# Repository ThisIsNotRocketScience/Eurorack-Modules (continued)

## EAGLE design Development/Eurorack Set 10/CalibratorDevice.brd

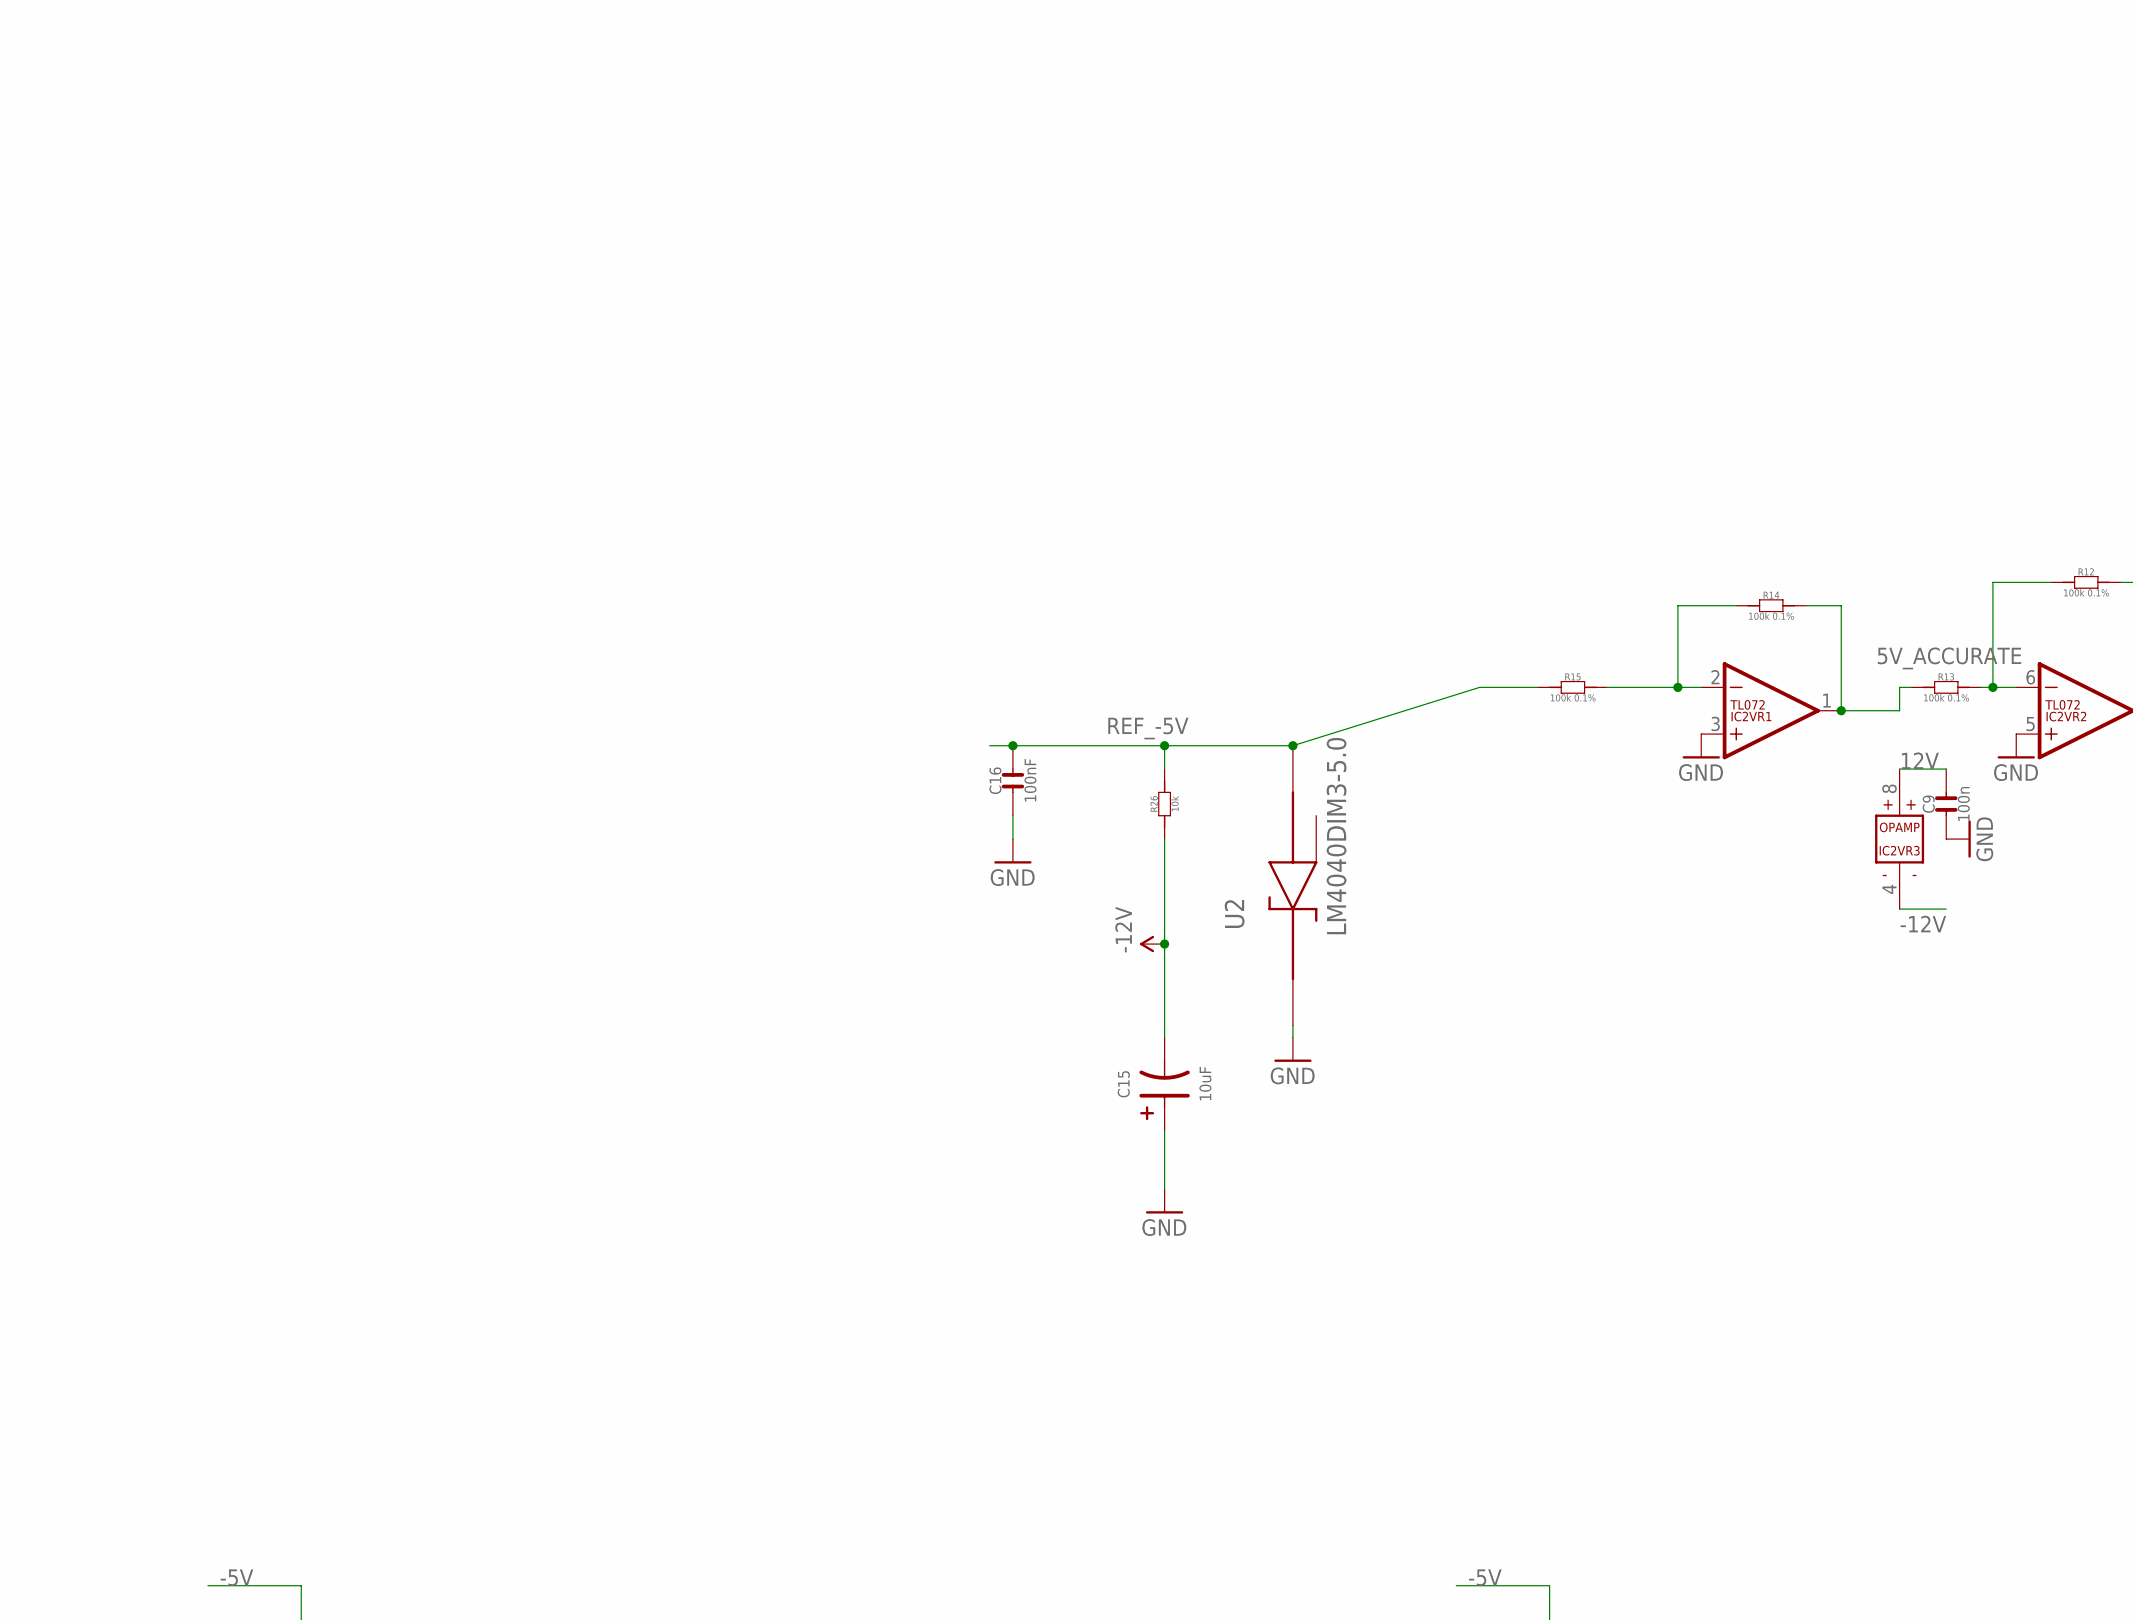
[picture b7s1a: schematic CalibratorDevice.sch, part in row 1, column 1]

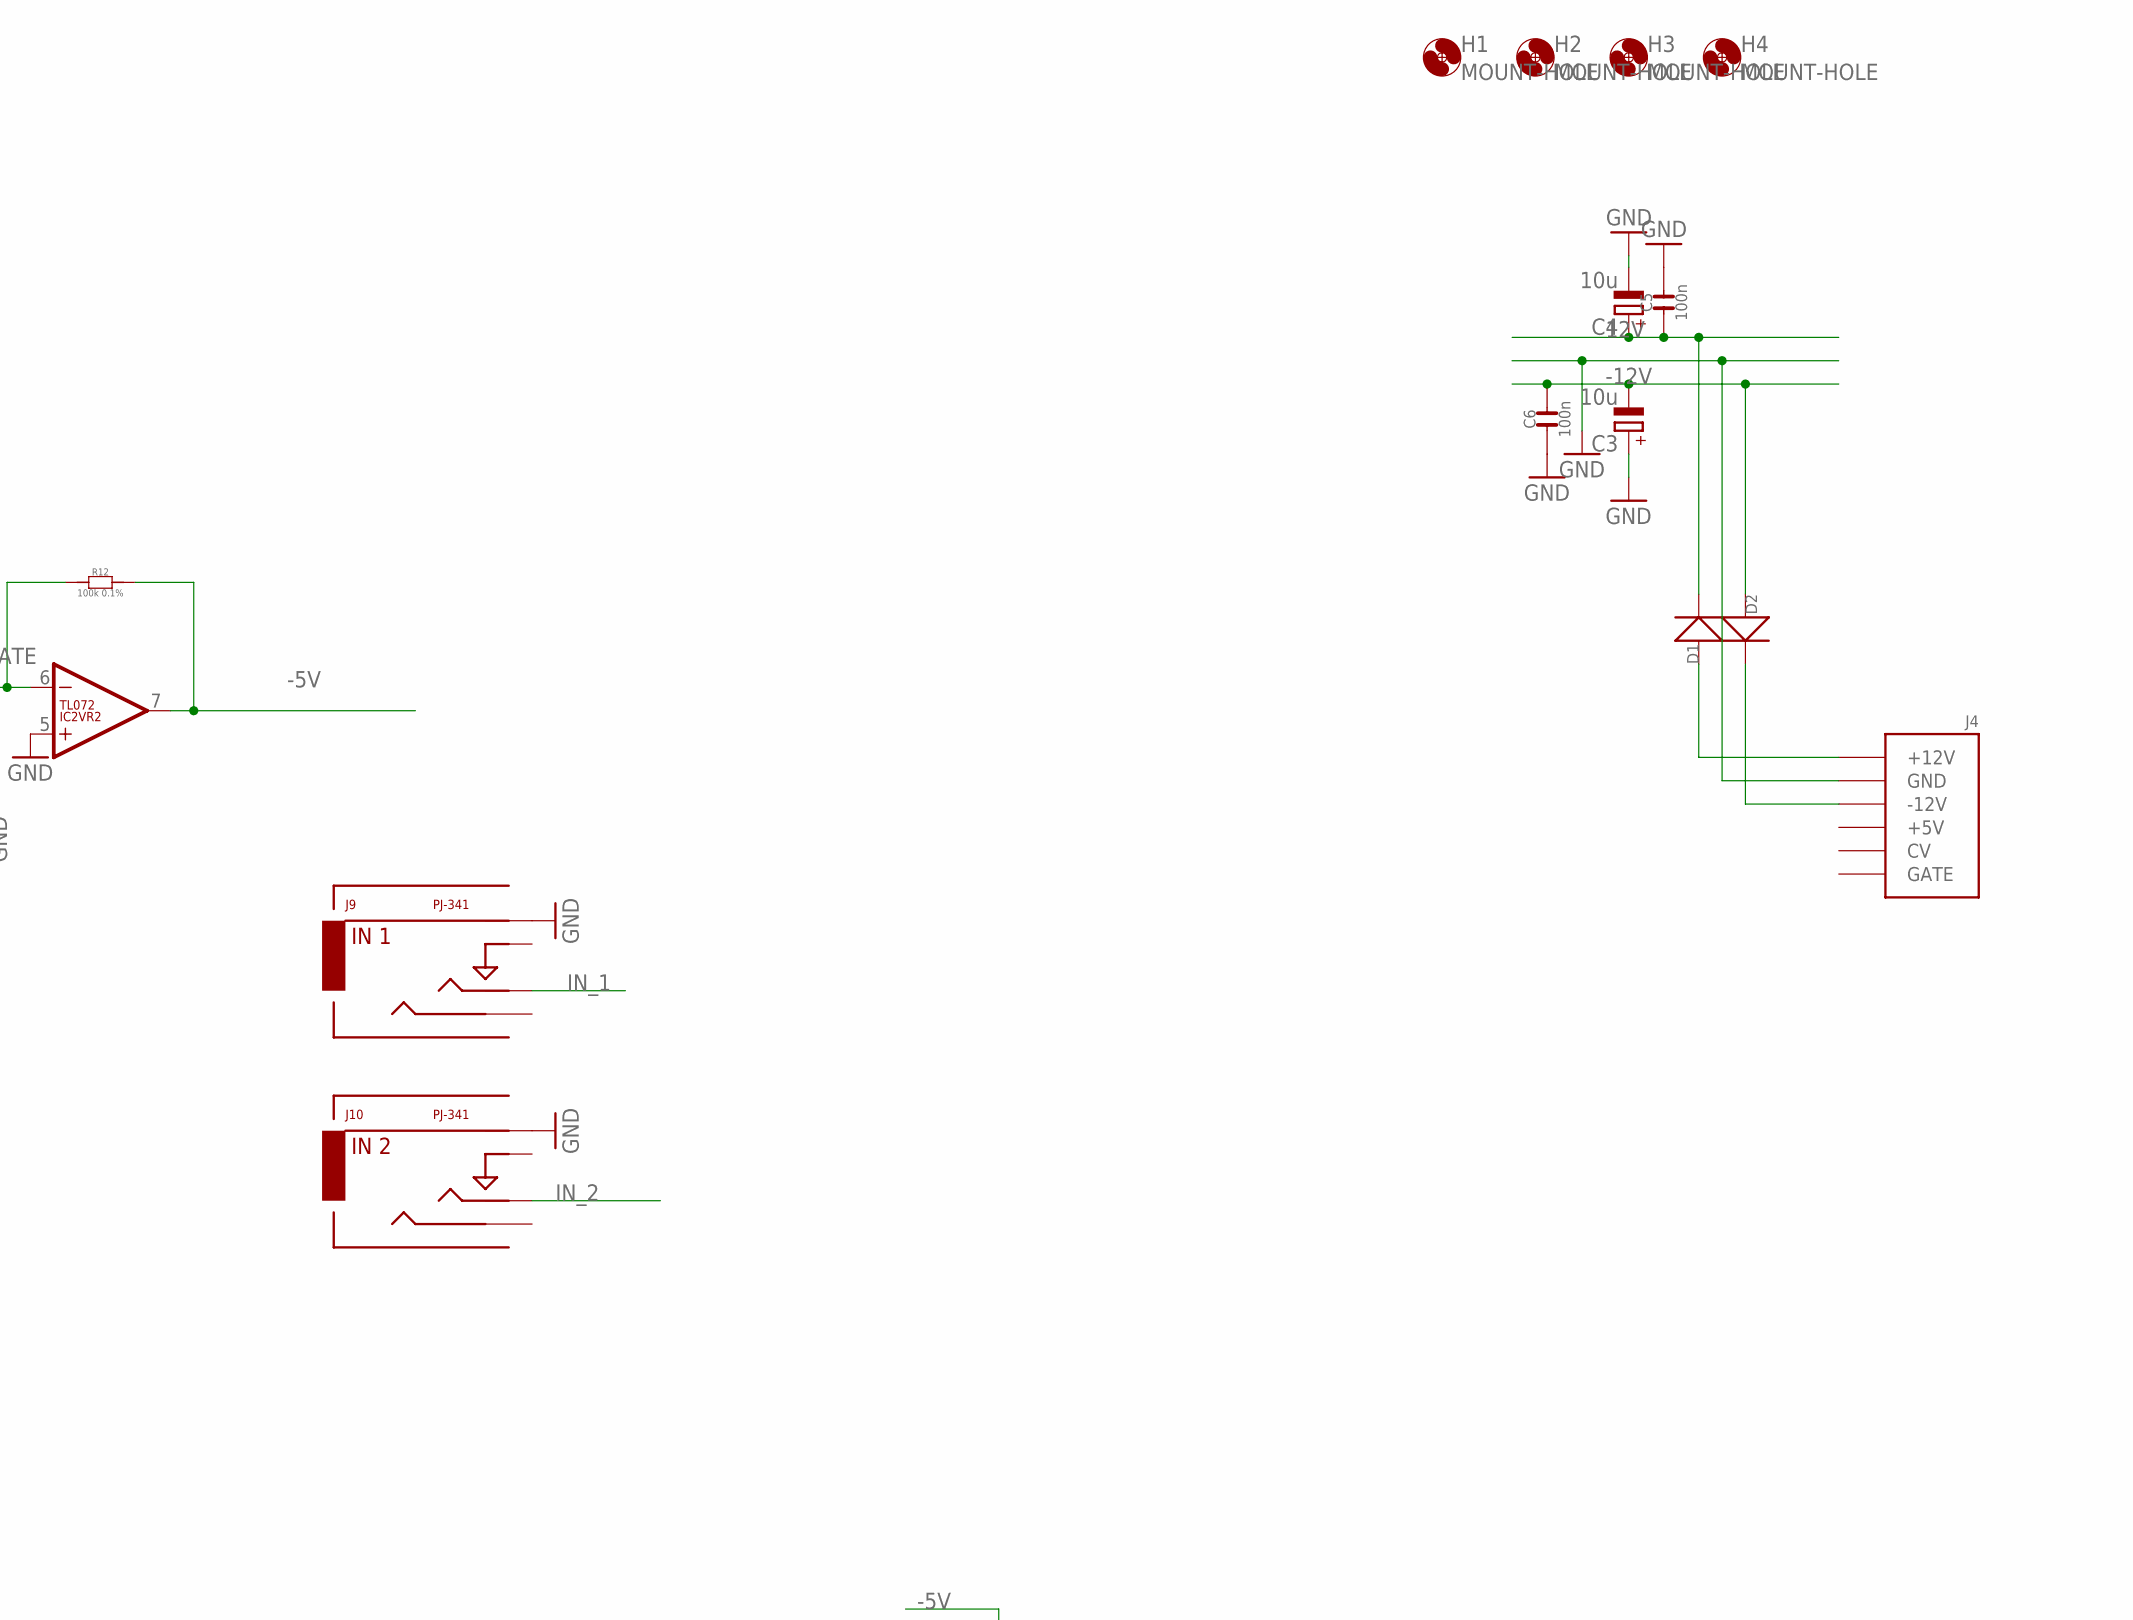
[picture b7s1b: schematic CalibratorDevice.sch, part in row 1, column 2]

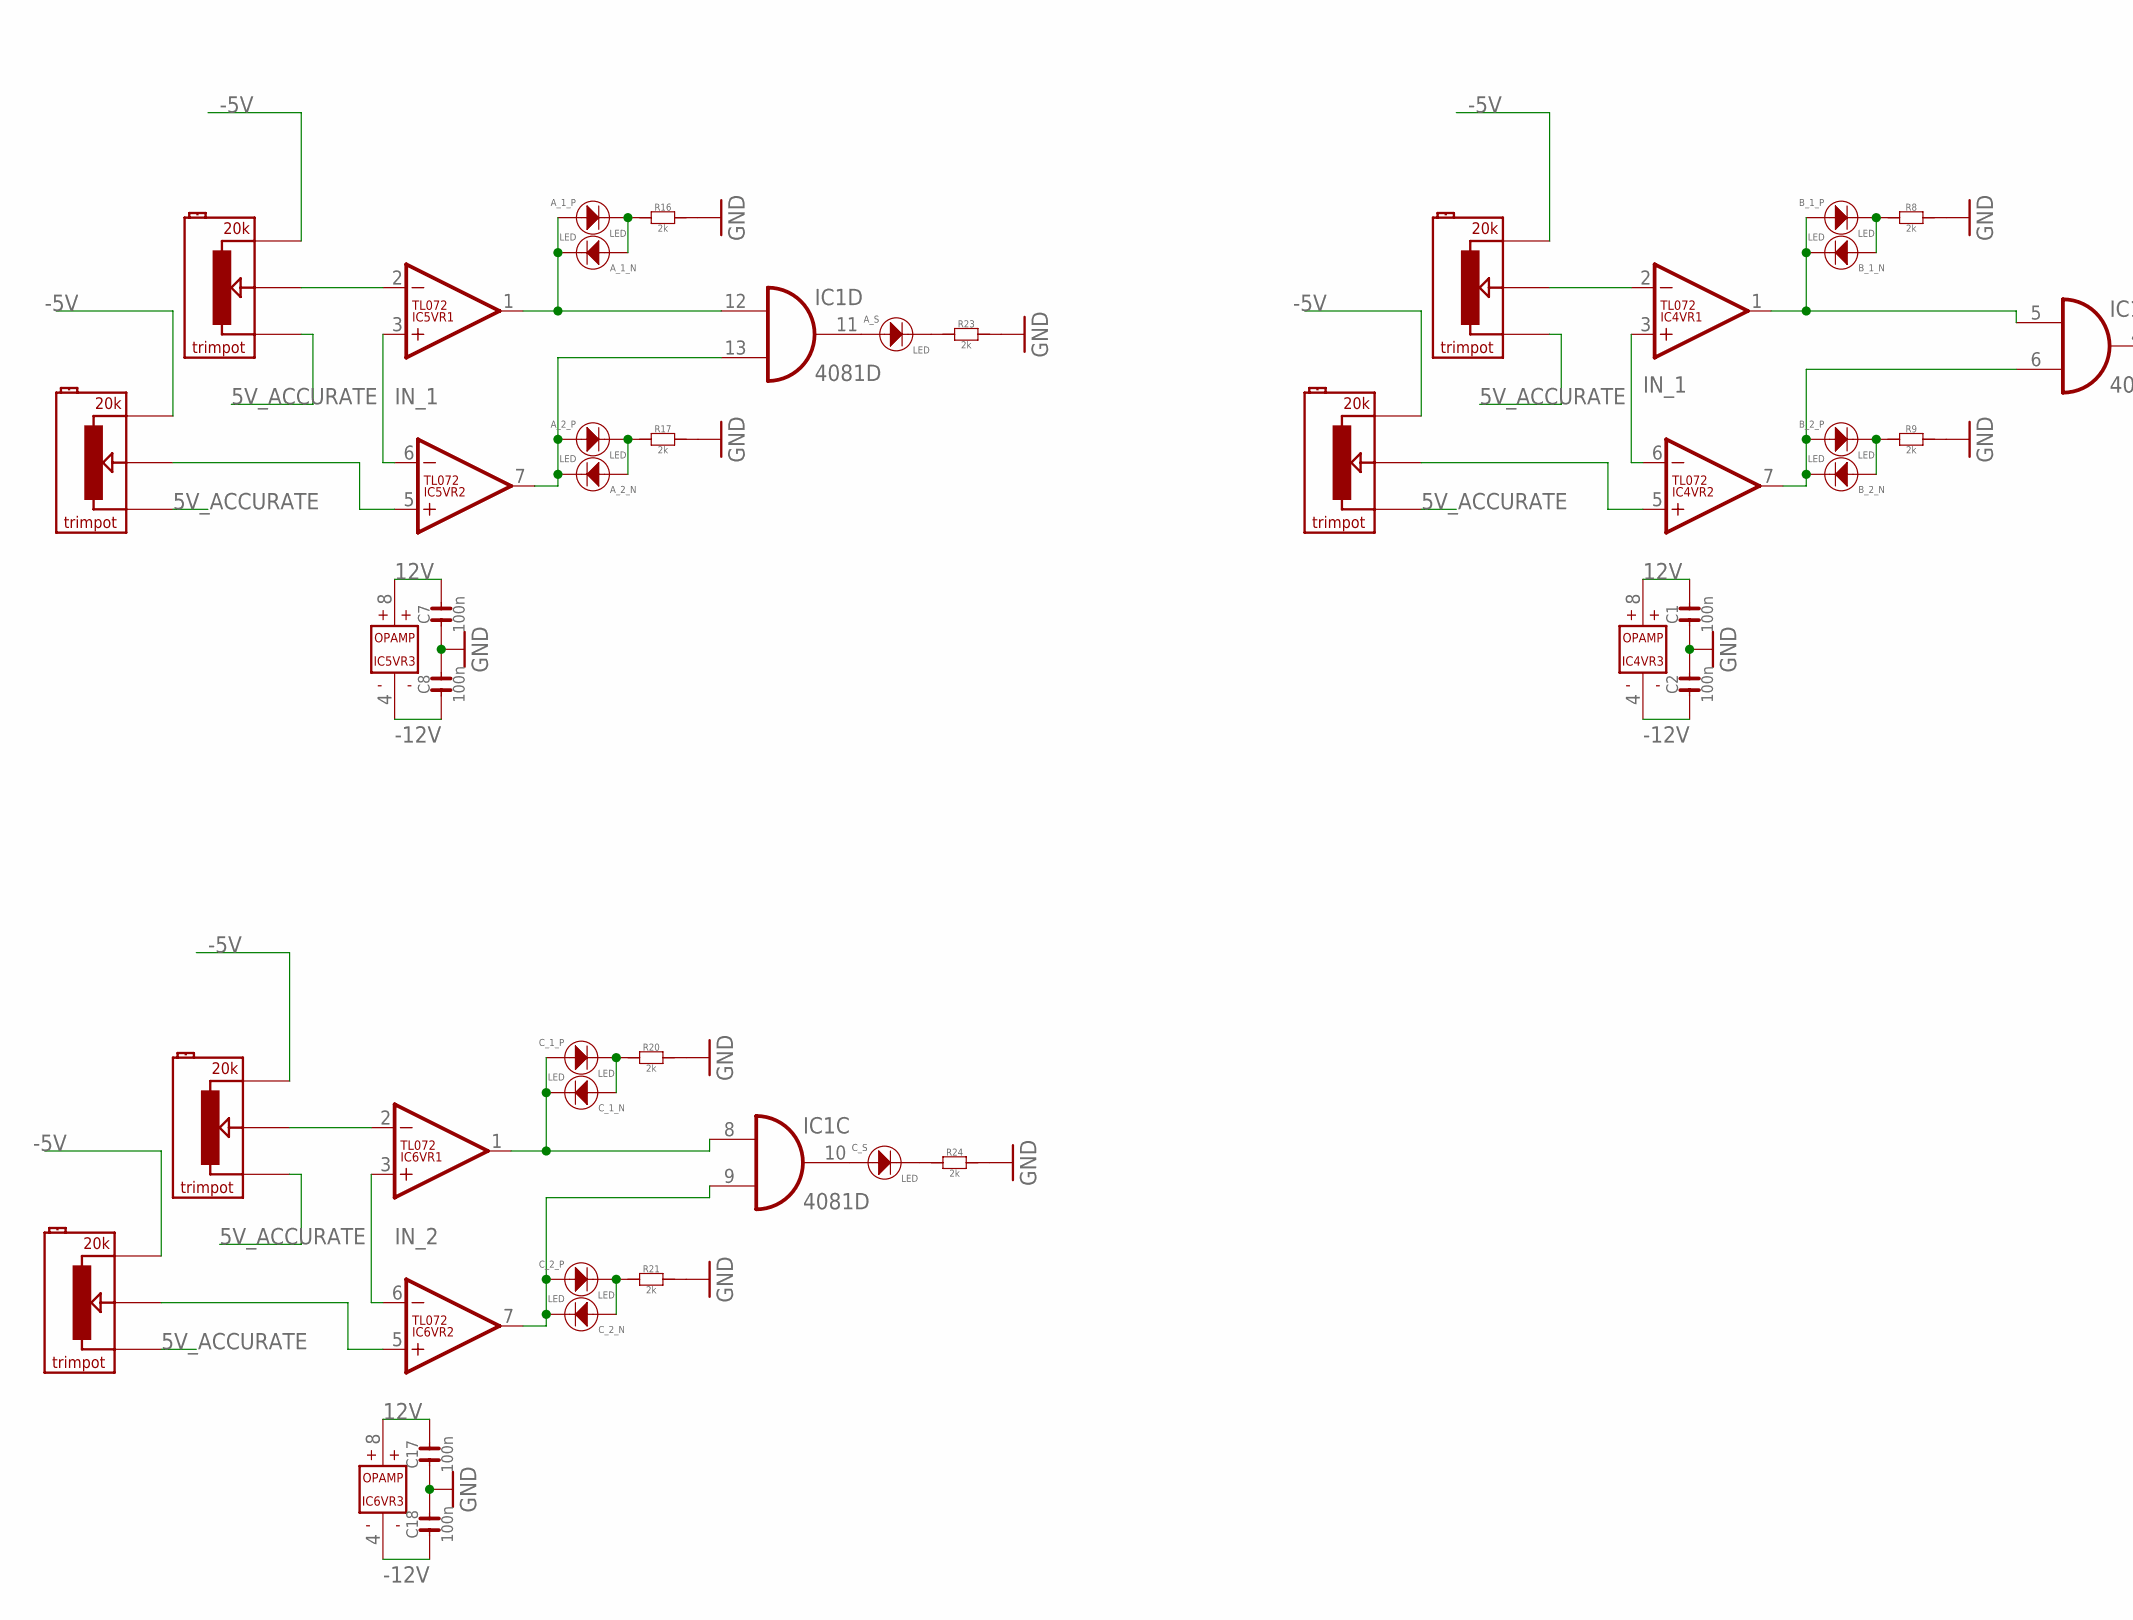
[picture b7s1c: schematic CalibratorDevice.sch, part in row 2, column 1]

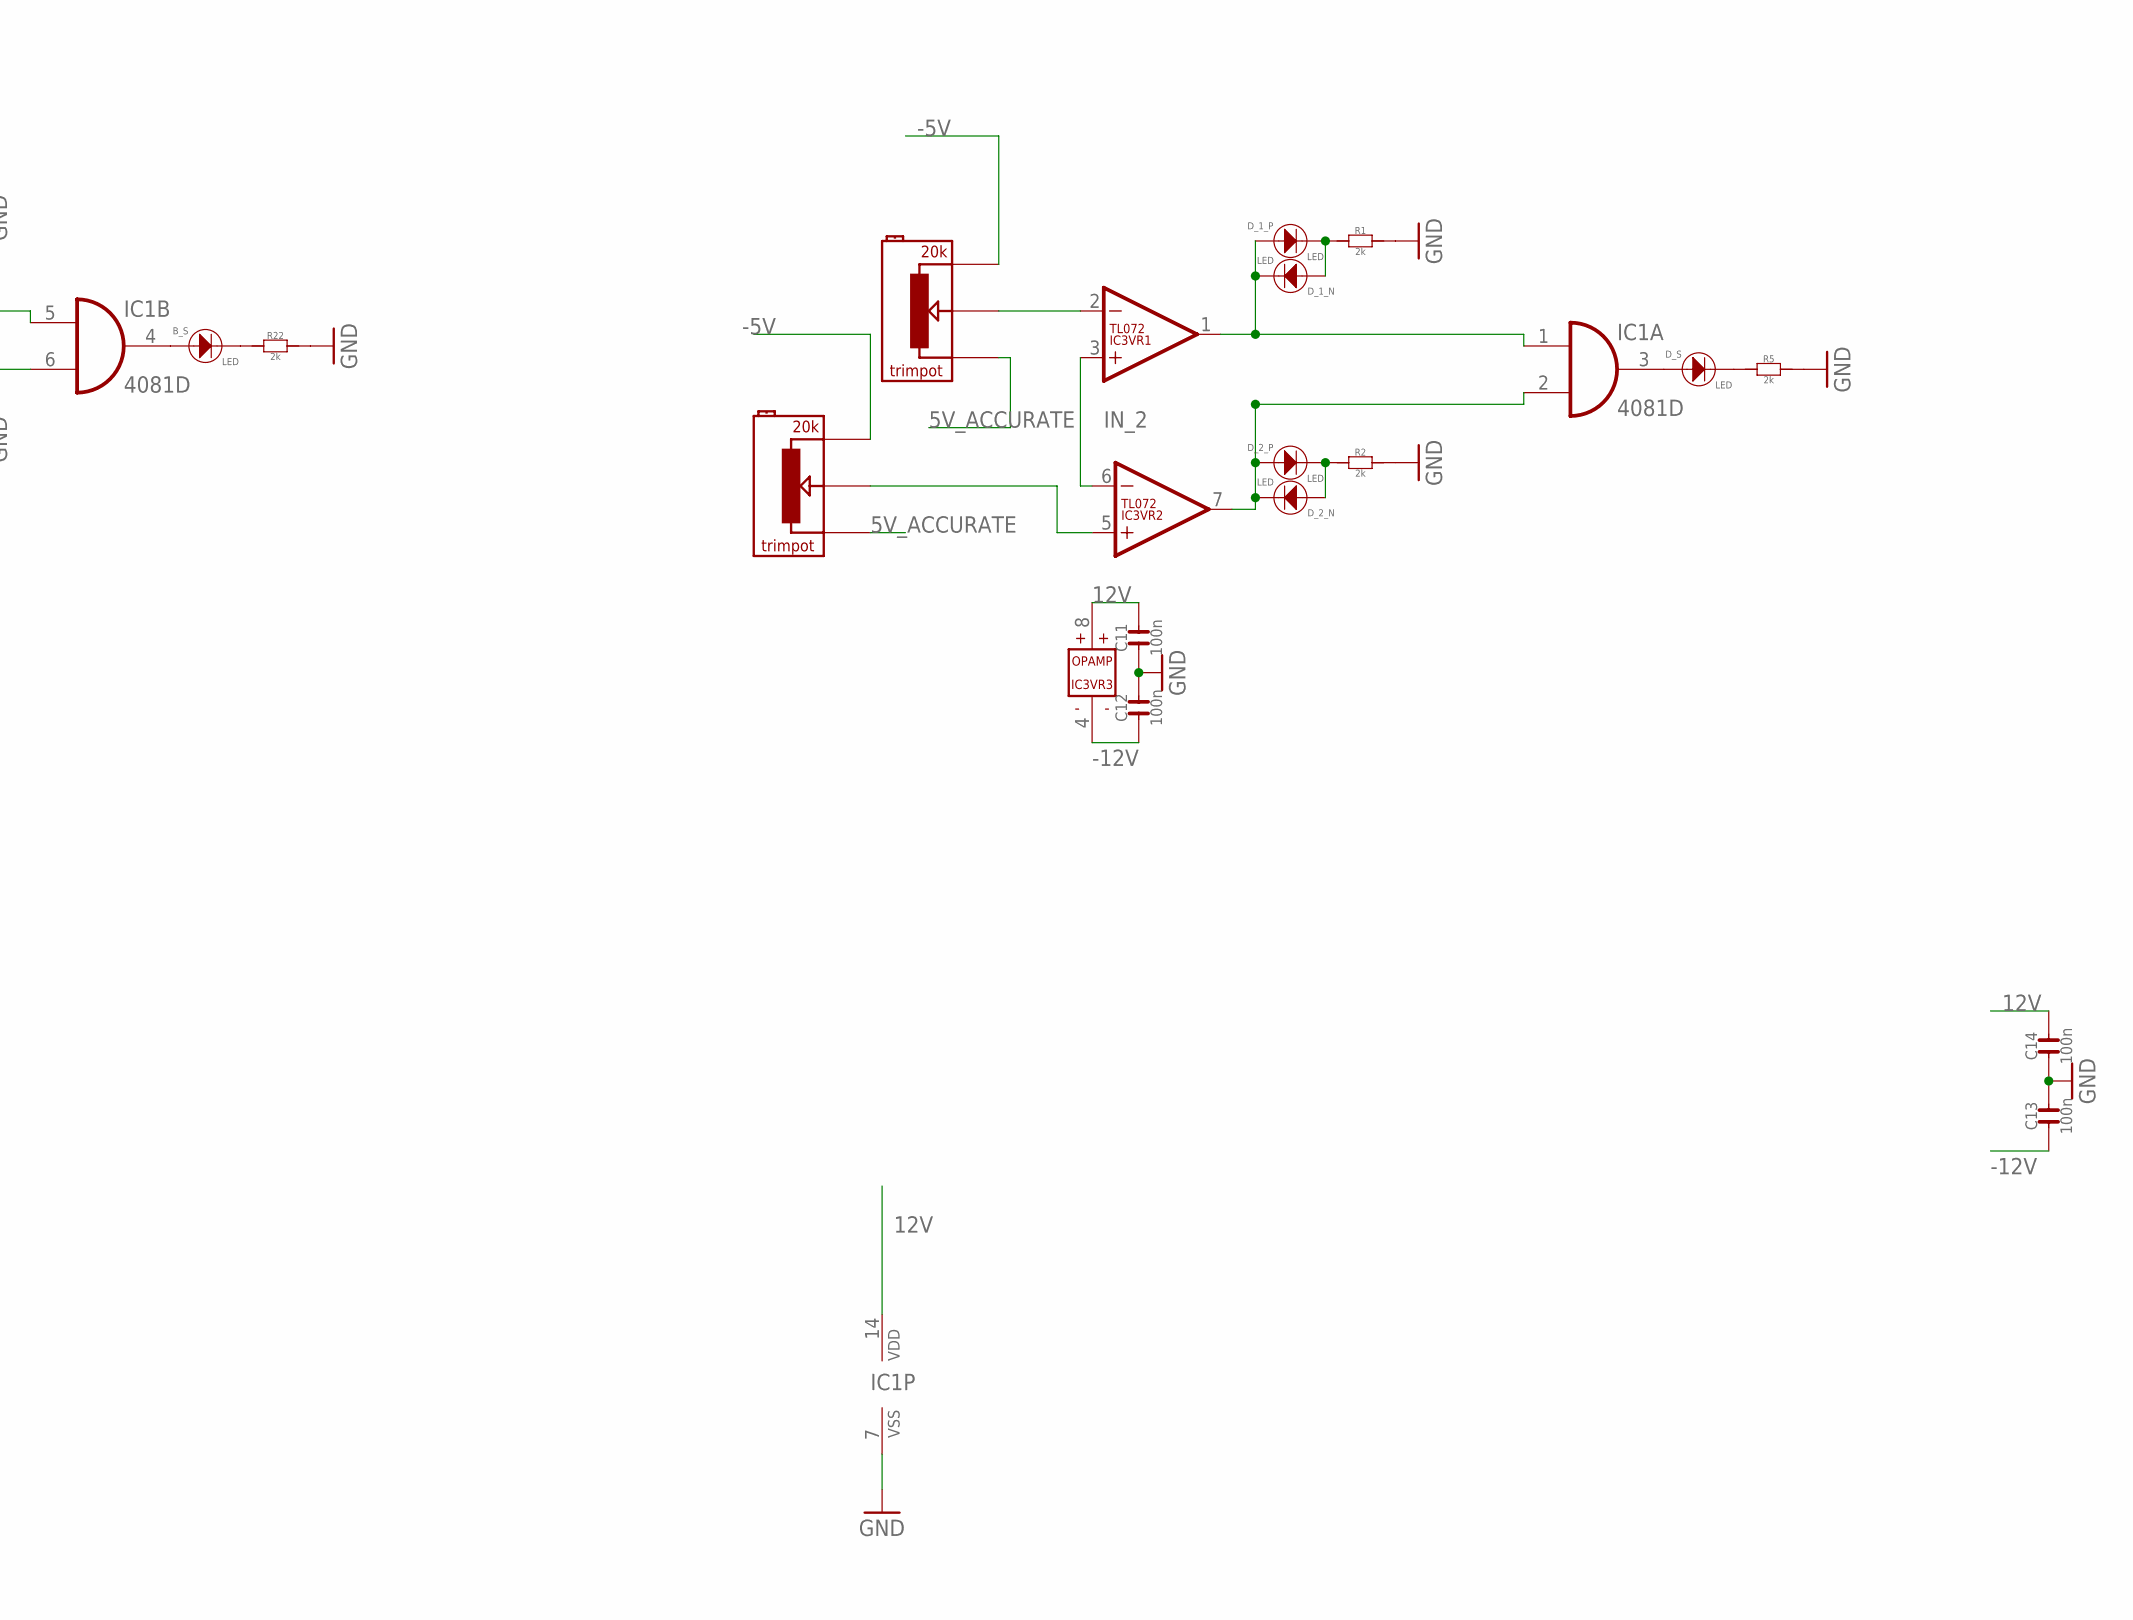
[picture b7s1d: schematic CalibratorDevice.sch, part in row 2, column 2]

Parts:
A_1_N, A_1_P, A_2_N, A_2_P: LED; 3MMLED
A_NEG: 20k; TRIMPOT
A_POS: 20k; TRIMPOT
A_S: LED; 3MMLED
B_1_N, B_1_P, B_2_N, B_2_P: LED; 3MMLED
B_NEG: 20k; TRIMPOT
B_POS: 20k; TRIMPOT
B_S: LED; 3MMLED
C1, C2, C5, C6, C7, C8, C9, C11, C12, C13, C14, C17, C18: 100n; C0603
C3, C4: 10u; CASE_B
C15: 10uF; CASE-A_3216; MPN TAJB106K020RNJ
C16: 100nF; C0603; MPN 06035C104KAT2A
C_1_N, C_1_P, C_2_N, C_2_P: LED; 3MMLED
C_NEG: 20k; TRIMPOT
C_POS: 20k; TRIMPOT
C_S: LED; 3MMLED
D1, D2: D-SMA; DO-214AC
D_1_N, D_1_P, D_2_N, D_2_P: LED; 3MMLED
D_NEG: 20k; TRIMPOT
D_POS: 20k; TRIMPOT
D_S: LED; 3MMLED
H1, H2, H3, H4: MOUNT-HOLE; 3.2-NOMARKINGS-SMALLSAFEZONE
IC1: 4081D; SO14
IC2, IC3, IC4, IC5, IC6: TL072; SO08
J4: POWER_SHROUDED_NOTEXT; POWER_16_SHROUDED_NOTEXT
J9, J10: PJ-341; 3.5MM-JACK-SWITCH-13MM-INPUT
R1, R2, R5, R8, R9, R16, R17, R20, R21, R22, R23, R24: 2k; R0603
R12, R13, R14, R15: 100k 0.1%; R0603
R26: 10k; R0603
U2: LM4040DIM3-5.0; SOT95P237X112-3N

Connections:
5V_ACCURATE: A_NEG.P$1, A_POS.P$1, B_NEG.P$1, B_POS.P$1, C_NEG.P$1, C_POS.P$1, D_NEG.P$1, D_POS.P$1, IC2.1 (OUT), R13.1, R14.2
12V: C1.2, C4.+, C5.1, C7.2, C9.2, C11.2, C14.2, C17.2, D1.2 (-), IC1.14 (VDD), IC2.8 (V+), IC3.8 (V+), IC4.8 (V+), IC5.8 (V+), IC6.8 (V+)
-5V: A_NEG.P$3, A_POS.P$3, B_NEG.P$3, B_POS.P$3, C_NEG.P$3, C_POS.P$3, D_NEG.P$3, D_POS.P$3, IC2.7 (OUT), R12.2
-12V: C2.1, C3.-, C6.2, C8.1, C12.1, C13.1, C15.- (2), C18.1, D2.1 (+), IC2.4 (V-), IC3.4 (V-), IC4.4 (V-), IC5.4 (V-), IC6.4 (V-), R26.1
GND: C1.1, C2.2, C3.+, C4.-, C5.2, C6.1, C7.1, C8.2, C9.1, C11.1, C12.2, C13.2, C14.1, C15.+ (1), C16.1, C17.1, C18.2, IC1.7 (VSS), IC2.3 (+IN), IC2.5 (+IN), J4.3 (GND), J4.4 (GND), J4.5 (GND), J4.6 (GND), J4.7 (GND), J4.8 (GND), J9.RING@3 (RING), J10.RING@3 (RING), R1.2, R2.2, R5.2, R8.2, R9.2, R16.2, R17.2, R20.2, R21.2, R22.2, R23.2, R24.2, U2.1 (CATHODE)
IN_1: IC4.3 (+IN), IC4.6 (-IN), IC5.3 (+IN), IC5.6 (-IN), J9.TIP@3 (TIP)
IN_2: IC3.3 (+IN), IC3.6 (-IN), IC6.3 (+IN), IC6.6 (-IN), J10.TIP@3 (TIP)
unnamed: D_1_N.+, D_1_P.-, R1.1
unnamed: D_NEG.P$2, IC3.2 (-IN)
unnamed: IC2.2 (-IN), R14.1, R15.2
unnamed: D_2_N.+, D_2_P.-, R2.1
unnamed: D_POS.P$2, IC3.5 (+IN)
unnamed: D_2_N.-, D_2_P.+, IC1.2 (I1), IC3.7 (OUT)
unnamed: IC2.6 (-IN), R12.1, R13.2
unnamed: D1.1 (+), J4.9 (+12V), J4.10 (+12V)
unnamed: D_1_N.-, D_1_P.+, IC1.1 (I0), IC3.1 (OUT)
unnamed: D_S.+, IC1.3 (O)
unnamed: D_S.-, R5.1
unnamed: B_1_N.-, B_1_P.+, IC1.5 (I0), IC4.1 (OUT)
unnamed: B_NEG.P$2, IC4.2 (-IN)
unnamed: B_1_N.+, B_1_P.-, R8.1
unnamed: B_2_N.+, B_2_P.-, R9.1
unnamed: B_2_N.-, B_2_P.+, IC1.6 (I1), IC4.7 (OUT)
unnamed: D2.2 (-), J4.1 (-12V), J4.2 (-12V)
unnamed: B_POS.P$2, IC4.5 (+IN)
unnamed: A_1_N.-, A_1_P.+, IC1.12 (I0), IC5.1 (OUT)
unnamed: A_NEG.P$2, IC5.2 (-IN)
unnamed: A_1_N.+, A_1_P.-, R16.1
unnamed: A_2_N.+, A_2_P.-, R17.1
unnamed: A_2_N.-, A_2_P.+, IC1.13 (I1), IC5.7 (OUT)
unnamed: A_POS.P$2, IC5.5 (+IN)
unnamed: C_1_N.-, C_1_P.+, IC1.8 (I0), IC6.1 (OUT)
unnamed: C_NEG.P$2, IC6.2 (-IN)
unnamed: C_1_N.+, C_1_P.-, R20.1
unnamed: C_2_N.+, C_2_P.-, R21.1
unnamed: C_2_N.-, C_2_P.+, IC1.9 (I1), IC6.7 (OUT)
unnamed: C_POS.P$2, IC6.5 (+IN)
unnamed: B_S.-, R22.1
unnamed: A_S.-, R23.1
unnamed: C_S.-, R24.1
unnamed: B_S.+, IC1.4 (O)
unnamed: A_S.+, IC1.11 (O)
unnamed: C_S.+, IC1.10 (O)
REF_-5V: C16.2, R15.1, R26.2, U2.2 (ANODE)

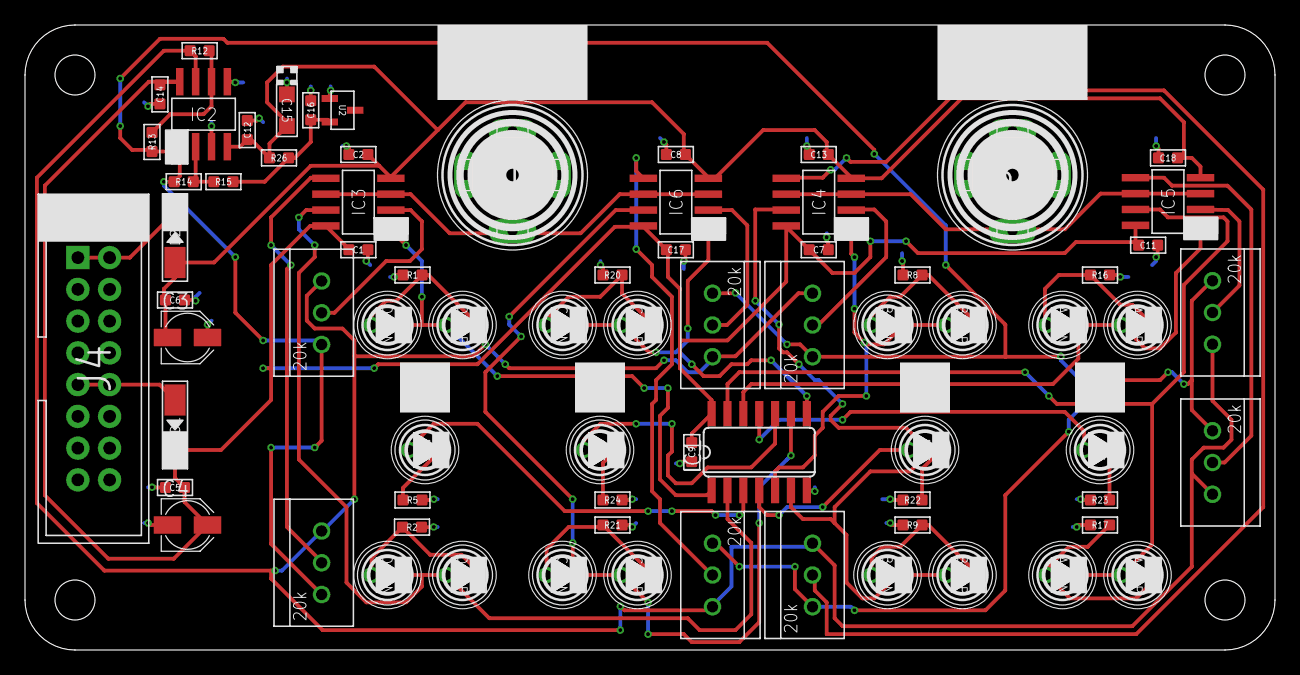
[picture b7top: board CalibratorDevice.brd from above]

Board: 2 copper layers, 100.0 x 50.0 mm, 78 parts (0 on the bottom side), 44 nets.

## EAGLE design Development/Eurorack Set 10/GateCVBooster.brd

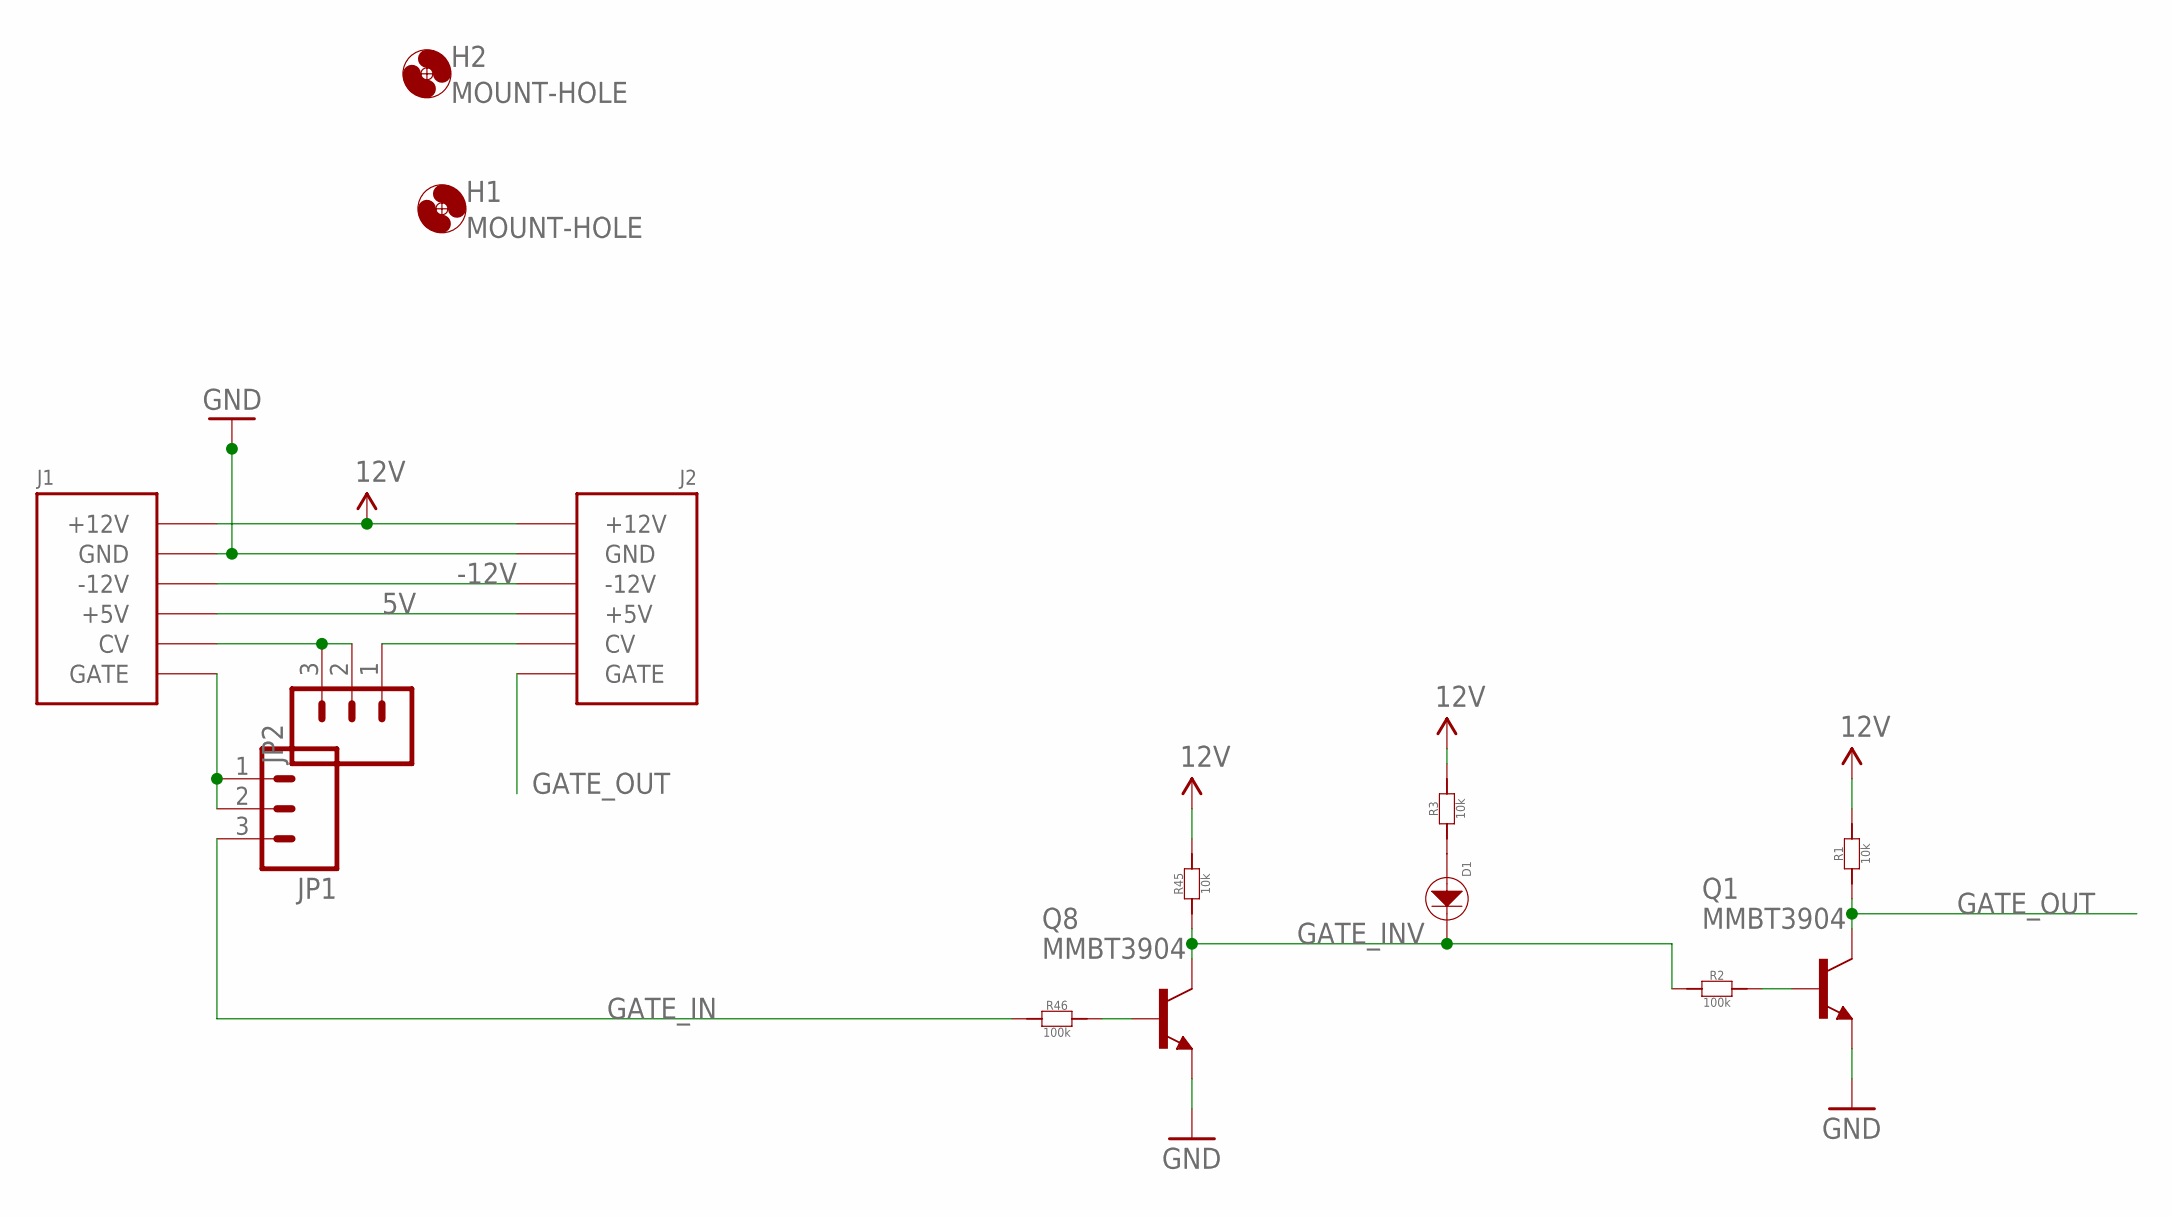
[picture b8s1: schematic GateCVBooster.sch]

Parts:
D1: LED; LED0603
H1, H2: MOUNT-HOLE; 3.2-NOMARKINGS-SMALLSAFEZONE
J1: POWERSHROUDED; POWER_16_SHROUDED
J2: POWER_SHROUDED_NOTEXT; POWER_16_SHROUDED_NOTEXT
JP1, JP2: M03PTH; 1X03
Q1, Q8: MMBT3904; SOT23-BEC; MPN PMBT3904,215
R1, R3, R45: 10k; R0603
R2, R46: 100k; R0603

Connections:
5V: J1.11 (+5V), J1.12 (+5V), J2.11 (+5V), J2.12 (+5V)
12V: J1.9 (+12V), J1.10 (+12V), J2.9 (+12V), J2.10 (+12V), R1.2, R3.2, R45.2
-12V: J1.1 (-12V), J1.2 (-12V), J2.1 (-12V), J2.2 (-12V)
GATE_IN: JP1.3, R46.1
GATE_INV: D1.-, Q8.C, R2.1, R45.1
GATE_OUT: J2.15 (GATE), J2.16 (GATE), Q1.C, R1.1
GND: J1.3 (GND), J1.4 (GND), J1.5 (GND), J1.6 (GND), J1.7 (GND), J1.8 (GND), J2.3 (GND), J2.4 (GND), J2.5 (GND), J2.6 (GND), J2.7 (GND), J2.8 (GND), Q1.E, Q8.E
unnamed: J1.15 (GATE), J1.16 (GATE), JP1.1, JP1.2
unnamed: J1.13 (CV), J1.14 (CV), JP2.2, JP2.3
unnamed: D1.+, R3.1
unnamed: J2.13 (CV), J2.14 (CV), JP2.1
unnamed: Q1.B, R2.2
unnamed: Q8.B, R46.2

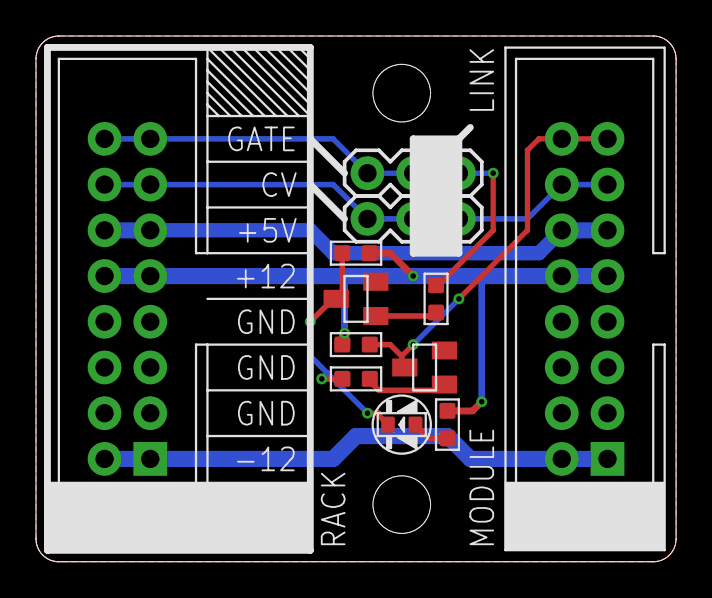
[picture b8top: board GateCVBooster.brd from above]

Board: 2 copper layers, 35.6 x 29.2 mm, 14 parts (0 on the bottom side), 13 nets.
